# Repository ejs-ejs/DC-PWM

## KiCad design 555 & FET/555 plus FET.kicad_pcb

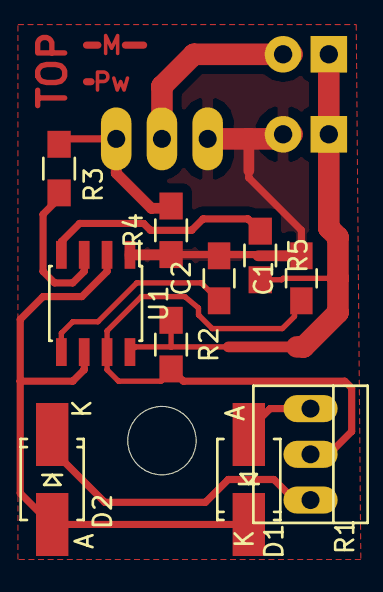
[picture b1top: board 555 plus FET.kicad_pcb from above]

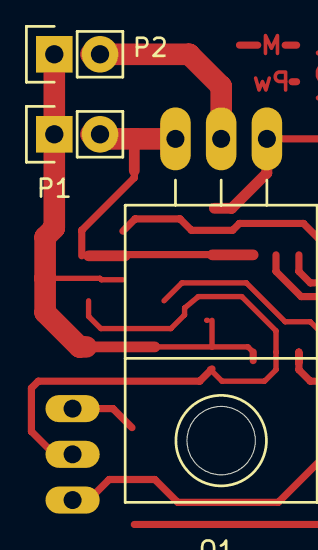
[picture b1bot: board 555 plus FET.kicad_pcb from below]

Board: 2 copper layers, 13 parts (3 on the bottom side), 10 nets.

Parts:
C1: 103; C_0805_HandSoldering
C2: 104; C_0805_HandSoldering
D1, D2: 1N4148; SMA_Handsoldering
P1: Power; Pin_Header_Straight_1x02
P2: Motor; Pin_Header_Straight_1x02
Q1: IRF510; TO-220_Neutral123_Horizontal_LargePads
R1: 100k; PINHEAD1-3
R2: 1k; R_0805_HandSoldering
R3: 330; R_0805_HandSoldering
R4: 470k; R_0805_HandSoldering
R5: 0R; R_0805_HandSoldering
U1: LM555N; SOIC-8_3.9x4.9mm_Pitch1.27mm

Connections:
GND: C1.2, C2.2, P1.2, Q1.3, R4.1, U1.1
unnamed: C1.1, R1.2, R2.2, U1.7
unnamed: C2.1, U1.5
unnamed: D1.1, D2.2, U1.2, U1.6
unnamed: D1.2, R1.1
unnamed: D2.1, R1.3
unnamed: P2.2, Q1.2
unnamed: Q1.1, R3.1, R4.2
unnamed: R3.2, U1.3
VCC: P1.1, P2.1, R2.1, R5.1, R5.2, U1.4, U1.8

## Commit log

2016-08-06 :lollipop: Added .gitattributes & .gitignore files
2016-08-06 initial commit
    NE555 and N-FET circuit. IRF510 N-FET in TO-220 casing mounted on the
    back side. PCB size c.a. 20x30 mm.
2016-08-06 Panelized F.Cu added
